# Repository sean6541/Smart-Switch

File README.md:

# Smart Switch

A complete smart switch designed with KiCAD and TinkerCAD.

**WARNING: THIS PROJECT INVOLVES MAINS VOLTAGES AND BRINGS WITH IT THE POTENTIAL FOR ELECTIC SHOCK. I AM NOT RESPONSIBE IF ANYTHING GOES WRONG.**

**NOTICE: The maximum current this device can handle safely is around 10 Amps. You might be able to push this to 15 Amps by adding lines of solder to the power traces on the PCB and switching to #16 or #14 AWG wire, however I have not tested this.**

## Schematic and PCB

**NOTE: You will need to have KiCAD installed in order to view/plot the PCB.**

The circuit schematic and PCB can be found within the [Schematic](https://github.com/sean6541/Smart-Switch/tree/master/Schematic) directory.
For the mains input I sacrificed the lead from a power bar but any 3-wire cord with a plug on the end will work.
The enclosure fits most NEMA 5-15R receptacles. (NOTE: You might have to break off the drywall "ears" for it to fit)

Manufacture and assembly should be pretty straightforward if you have done this kind of thing before.

## Enclosure

The 3D-printable enclosure is located within the [Enclosure](https://github.com/sean6541/Smart-Switch/tree/master/Enclosure) directory.
There is a multitude of methods for mounting the PCB within the enclosure and affixing the two halves together, however I recommend hot glue for the PCB and colored duct tape for the enclosure. You may also use glue.
**IMPORTANT: Remember to always place some form of non-conductive material between the PCB and receptacle to ensure good isolation! A few layers of Kapton tape works well for this purpose.**
The receptacle just screws into place from the inside with the screws almost but not quite poking through the front.

You will also have to drill a hole for the incoming mains supply lead. I intentionally left this part out of the enclosure design due to the various different sizes of wire that may be used.

## Program

At the heart of the smart switch is an Espressif ESP8266 WiFi-enabled microcontroller. Pulling GPIO 5 low enables the power and pulling it high disables it. The program flashed onto the ESP8266 may vary, however if you decide to use the [ESPHome](https://esphome.io) firmware, a basic configuration is provided below:
```
esphome:
  name: smart_switch
  platform: ESP8266
  board: nodemcuv2

wifi:
  ssid: "your_wifi_ssid"
  password: "your_wifi_password"

api:

ota:

switch:
  - platform: gpio
    pin:
      number: GPIO5
      inverted: True
    name: Smart Switch
```

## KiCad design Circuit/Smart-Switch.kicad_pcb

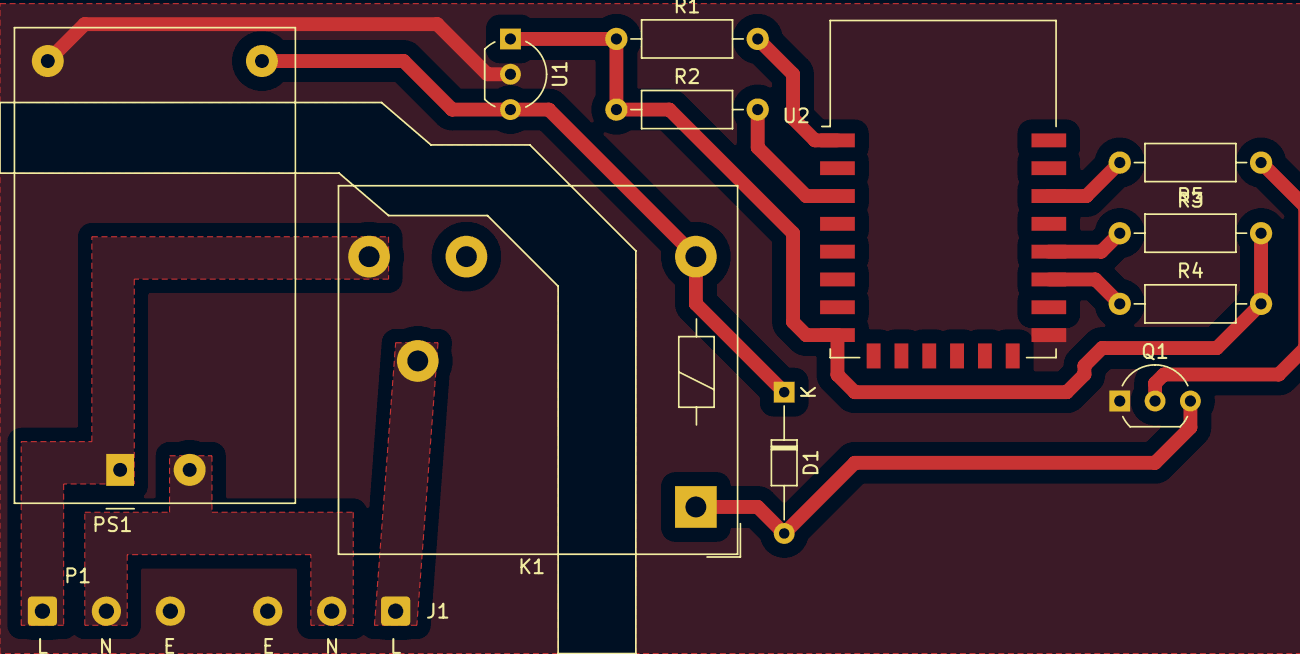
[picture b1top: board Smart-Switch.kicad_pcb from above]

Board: 2 copper layers, 13 parts (0 on the bottom side), 14 nets.

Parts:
D1: D; D_DO-34_SOD68_P10.16mm_Horizontal
J1: Conn_WallSocket_Earth; SolderWire-0.5sqmm_1x03_P4.6mm_D0.9mm_OD2.1mm
K1: FINDER-40.11; Relay_SPDT_Finder_40.11
P1: Conn_WallPlug_Earth; SolderWire-0.5sqmm_1x03_P4.6mm_D0.9mm_OD2.1mm
PS1: HLK-PM01; Converter_ACDC_HiLink_HLK-PMxx
Q1: Q_NPN_EBC; TO-92_Inline_Wide
R1, R2, R3, R4: 10k; R_Axial_DIN0207_L6.3mm_D2.5mm_P10.16mm_Horizontal
R5: 1k; R_Axial_DIN0207_L6.3mm_D2.5mm_P10.16mm_Horizontal
U1: L78L33_TO92; TO-92_Inline_Wide
U2: ESP-12E

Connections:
+3V3: R1.1, R2.1, R3.2, R4.2, U1.1, U2.8
+5V: D1.1, K1.A2, PS1.4, U1.3
GND: PS1.3, Q1.1, U1.2, U2.15
unnamed: D1.2, K1.A1, Q1.3
unnamed: J1.1, K1.11
unnamed: J1.2, P1.2, PS1.2
unnamed: J1.3, P1.3
unnamed: K1.14, P1.1, PS1.1
unnamed: Q1.2, R5.1
unnamed: R1.2, U2.1
unnamed: R2.2, U2.3
unnamed: R3.1, U2.18
unnamed: R4.1, U2.17
unnamed: R5.2, U2.20

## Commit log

2020-06-24 Fix README
